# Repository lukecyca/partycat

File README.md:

partycat led controller
=======================

Partycat is a small ESP8266-based controller for WS2812 LED strips.

Features
--------

- Level-shifted GPIO pins, including one for a WS2812 strip
- A footprint that lets you solder the end of the strip right to the board
- WS2812 is on the I2S port, so it can use DMA using this hack (or the Arduino-compatible version)
- Programming using a standard 6-pin FTDI cable (no onboard USB you wuss)

Illustration Credit: http://nedroid.com/2009/05/party-cat-full-series/

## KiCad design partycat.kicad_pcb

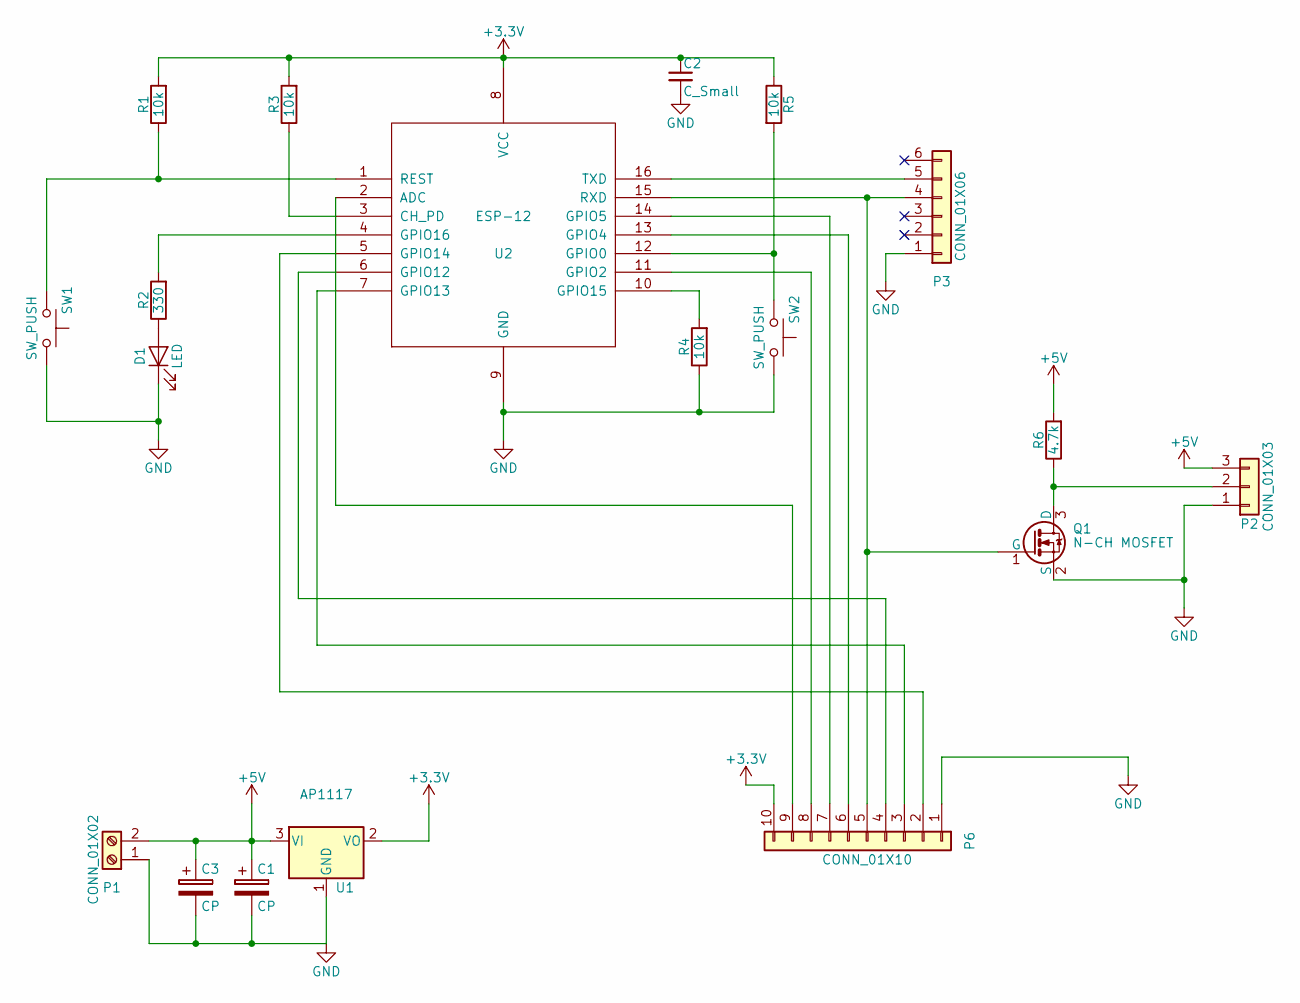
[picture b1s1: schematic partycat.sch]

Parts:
C1: CP; CP_Radial_D12.5mm_P5.00mm
C2: C_Small; C_0603_HandSoldering
C3: CP; CP_Radial_D5.0mm_P2.50mm
D1: LED; LED_0805
P1: CONN_01X02; TerminalBlock_Pheonix_MKDS1.5-2pol
P2: CONN_01X03; WS2812_Strip
P3: CONN_01X06; Pin_Header_Straight_1x06
P6: CONN_01X10; Pin_Header_Straight_1x10
Q1: N-CH MOSFET; SOT-23
R1, R3, R4, R5: 10k; R_0603_HandSoldering
R2: 330; R_0603_HandSoldering
R6: 4.7k; R_0603_HandSoldering
SW1, SW2: SW_PUSH; SW_SPST_PTS645
U1: AP1117; SOT-223
U2: ESP-12; ESP-07v2-smd

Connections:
+3V3: C2.1, P6.10, R1.2, R3.2, R5.1, U1.2 (VO), U2.8 (VCC)
+5V: C1.1, C3.1, P1.2, P2.3, R6.2, U1.3 (VI)
GND: C1.2, C2.2, C3.2, D1.1 (K), P1.1, P2.1, P3.1, P6.1, Q1.2 (S), R4.1, SW1.1, SW2.1, U1.1 (GND), U2.9 (GND); also elsewhere on the board
unnamed: D1.2 (A), R2.1
unnamed: P2.2, Q1.3 (D), R6.1
unnamed 5: P3.4, P6.5, Q1.1 (G), U2.15 (RXD); also elsewhere on the board
unnamed 6: P3.5, U2.16 (TXD); also elsewhere on the board
unnamed: P6.2, U2.5 (GPIO14)
unnamed: P6.3, U2.7 (GPIO13)
unnamed: P6.4, U2.6 (GPIO12)
unnamed: P6.6, U2.13 (GPIO4)
unnamed: P6.7, U2.14 (GPIO5)
unnamed: P6.8, U2.11 (GPIO2)
unnamed: P6.9, U2.2 (ADC)
unnamed: R1.1, SW1.2, U2.1 (REST)
unnamed: R2.2, U2.4 (GPIO16)
unnamed: R3.1, U2.3 (CH_PD)
unnamed: R4.2, U2.10 (GPIO15)
unnamed: R5.2, SW2.2, U2.12 (GPIO0)

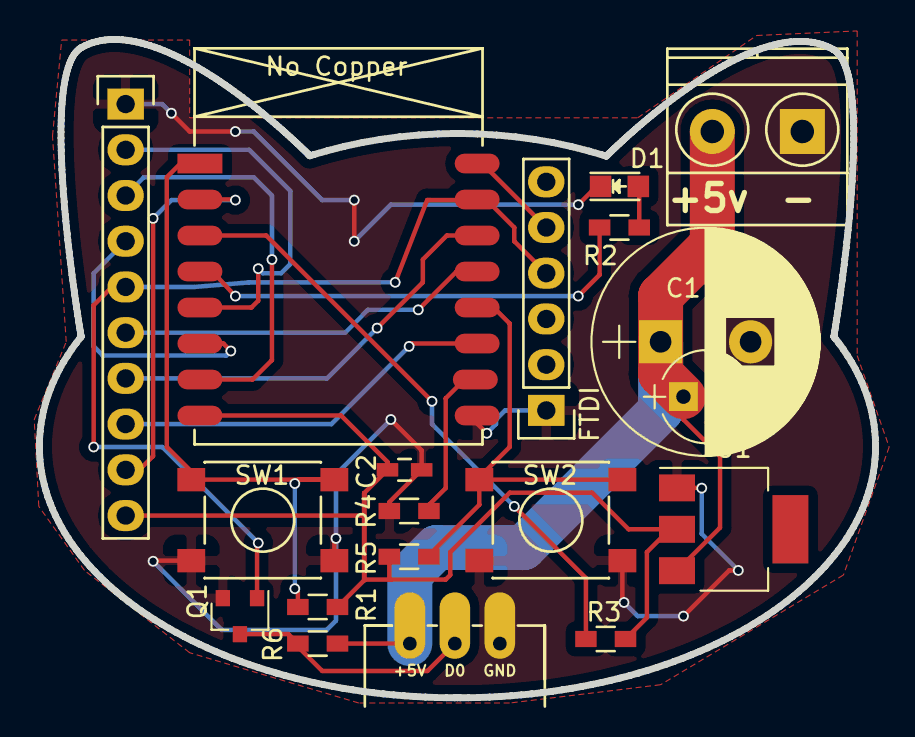
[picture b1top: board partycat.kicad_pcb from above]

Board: 2 copper layers, 46.5 x 36.6 mm, 19 parts (0 on the bottom side), 19 nets.

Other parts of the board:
FTDI: CONN_01X06; Pin_Header_Straight_1x06

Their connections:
GND: FTDI.1; also elsewhere on the board
unnamed 5: FTDI.4; also elsewhere on the board
unnamed 6: FTDI.5; also elsewhere on the board

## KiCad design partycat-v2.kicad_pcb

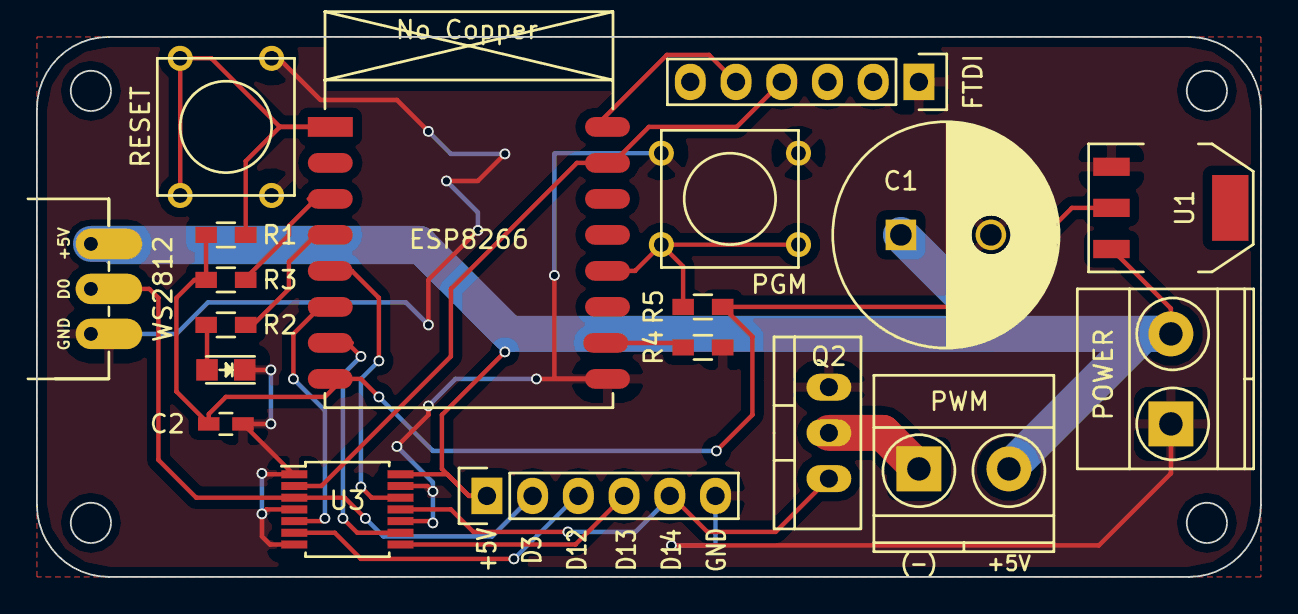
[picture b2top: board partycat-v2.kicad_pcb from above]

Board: 2 copper layers, 68.0 x 30.0 mm, 19 parts (0 on the bottom side), 19 nets.

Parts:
C1: CP; C_Radial_D12.5_L25_P5
C2: C_Small; C_0603_HandSoldering
D1: LED; LED_0805
FTDI: CONN_01X06; Pin_Header_Straight_1x06
P4: CONN_01X06; Pin_Header_Straight_1x06
PGM: SW_PUSH; SW_PUSH_SMALL
POWER: CONN_01X02; TerminalBlock_Pheonix_MKDS1.5-2pol
PWM: CONN_01X02; TerminalBlock_Pheonix_MKDS1.5-2pol
Q2: Q_NMOS_GDS; TO-220_Neutral123_Vertical
R1, R3, R4, R5: 10k; R_0603_HandSoldering
R2: 330; R_0603_HandSoldering
RESET: SW_PUSH; SW_PUSH_SMALL
U1: AP1117; SOT-223
U2: ESP-12; ESP-07v2-smd
U3: SN54AHCT125; TSSOP-14_4.4x5mm_Pitch0.65mm
WS2812: CONN_01X03; WS2812_Strip

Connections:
+3V3: C2.1, R1.2, R3.2, R5.1, U1.2, U2.8
+5V: C1.1, P4.1, POWER.2, PWM.2, U1.3, U3.14, WS2812.3
GND: C1.2, C2.2, D1.1, FTDI.1, P4.6, PGM.1, POWER.1, Q2.3, R4.1, RESET.1, U1.1, U2.9, U3.1, U3.4, U3.7, U3.10, U3.13, WS2812.1
unnamed: D1.2, R2.1
unnamed: P4.2, U3.3, WS2812.2
unnamed: FTDI.4, U2.15, U3.2
unnamed: FTDI.5, U2.16
unnamed: P4.3, U3.6
unnamed: P4.4, U3.8
unnamed: P4.5, Q2.1, U3.11
unnamed: PWM.1, Q2.2
unnamed: R1.1, RESET.2, U2.1
unnamed: R3.1, U2.3
unnamed: R2.2, U2.4
unnamed: R4.2, U2.10
unnamed: PGM.2, R5.2, U2.12
unnamed: U2.5, U3.12
unnamed: U2.6, U3.5
unnamed: U2.7, U3.9

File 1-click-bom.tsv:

References	Qty	Description	Part Number
C1	1	CP Polarised capacitor C Radial D12.5 L25 P5	399-6102-ND
C2	1	C Small Unpolarized capacitor 0603 HandSoldering	311-3700-1-ND
D1	1	LED 0805	160-1427-1-ND
"P1, P5"	2	CONN 01X02 Connector 01x02 TerminalBlock Pheonix MKDS1.5-2pol	
P2	1	CONN 01X03 Connector 01x03 WS2812 Strip	104990000-ND
"P4, P3"	2	CONN 01X06 Connector 01x06 Pin Header Straight 1x06	
Q2	1	Q NMOS GDS Transistor N-MOSFET (general) TO-220 Neutral123 Vertical	497-3185-5-ND
R2	1	R 330 Resistor 0603 HandSoldering	CR0603-JW-331ELFCT-ND
"R4, R3, R5, R1"	4	R 10k Resistor 0603 HandSoldering	CR0603-JW-103ELFCT-ND
"SW2, SW1"	2	SW PUSH Button SMALL	679-2428-ND
U1	1	"AP1117 Fixed/Adjustable 1A Low Dropout regulator, Positive SOT-223"	AZ1117IH-ADJTRG1DICT-ND
U2	1	"ESP-12 ESP8622 module, 16 pins, 2mm, PCB antenna ESP-07v2-smd"	
U3	1	SN54AHCT125 SSOP-14	296-4653-1-ND

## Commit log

2016-11-01 README
2016-11-01 Wording
2016-11-01 Add kitnic.yml
2016-11-01 Move kitnic.yml to kitnic.yaml
    Sorry we don't support both extensions yet
2016-11-01 Added some Digikey part numbers to BOM
2017-06-13 Added docs, panelized gerbers, and renamed files (all versions will use this repo)
2018-10-04 Update 1-click-bom.tsv
    Added more digikey part numbers to BOM
2018-11-29 More v4 updates
2018-11-29 Add rev4 instruction sheet
2018-12-01 Add SVG of soldermask (for a stencil)
2018-12-02 Add solder paste DXF
2019-12-30 Correct heading in 1-click-bom
